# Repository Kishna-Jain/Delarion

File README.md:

# Delarion

### A custom CoreXY 3D printer: the best bang for your buck

Delarion is a CoreXY 3D printer designed to deliver near-premium performance without a premium price. It is built on a rigid **2020 aluminum extrusion** frame, with **ball screws** and **linear rails** for smooth, accurate motion, and runs **Klipper** on a custom **ESP32-S3** control board.

> **Status:** Design / pre-build. Submitted to Hack Club Stardance for funding.

---

## Table of Contents

1. [Why Delarion?](#why-delarion)
2. [Highlights](#highlights)
3. [Specifications](#specifications)
4. [Motion System](#motion-system)
5. [Electronics and Firmware](#electronics-and-firmware)
6. [Custom PCB](#custom-pcb)
7. [3D Model](#3d-model)
8. [Roadmap](#roadmap)
9. [Credits](#credits)

---

## Why Delarion?

Every maker eventually gets the urge to build random nerdy things from YouTube tutorials. I went down that road too, but without a 3D printer the workarounds get messy, and the final result lacks finesse: a pile of scraps in a makeshift enclosure. We've all been there.

So I went shopping for a cheap printer, and the results weren't great. Printers now start around $100 USD, but most of those are disappointing, and there is little reason to buy an Ender 3 today when almost everything is better. Bambu Lab is an option, and some budget machines exist, but still nothing fully satisfying. In my area, a *good* printer costs about **$500**, while the cheap ones are just cheap.

So the quest began: **build my own.** Delarion is the result.

## Highlights

- **CoreXY kinematics** for fast, light-toolhead motion
- **2020 aluminum extrusion frame**, sturdy, rigid and easy to source
- **Ball screws and linear rails** for smooth, precise, quiet movement
- **Klipper firmware** running on a host computer for high speed and advanced features
- **ESP32-S3 main MCU**, with Wi-Fi/BLE and plenty of room for experiments
- **TMC2208 stepper drivers** for quiet operation
- **MPU6050 accelerometer on the board** for input shaping / resonance tuning
- **Fully custom PCB**, designed from scratch

## Specifications

| Item | Detail |
|---|---|
| Kinematics | CoreXY |
| Frame | 2020 aluminum extrusion |
| Linear motion | Linear rails |
| Z motion | Ball screws |
| Motors | NEMA 17 steppers |
| Stepper drivers | TMC2208 |
| Main MCU | ESP32-S3 |
| Firmware | Klipper |
| Host | Raspberry Pi or any spare laptop/PC |
| Input power | 24 V clean DC supply |
| Logic power | 5 V external, 3.3 V regulated on-board (AMS1117-3.3) |
| Input shaping sensor | MPU6050 |
| Build volume | _TBD_ |
| Max speed / acceleration | _TBD_ |
| Hotend / extruder | Standard hotend and extruder (see `BOM.csv`) |

<!-- TODO: fill in the TBD rows as the design is finalised -->

## Motion System

CoreXY moves the toolhead in X and Y using two fixed motors and a crossed belt path. Because the motors are stationary, the moving mass is small, which allows higher accelerations and cleaner prints than a traditional bed slinger.

- **X/Y:** two NEMA 17 motors driving a CoreXY belt layout on linear rails
- **Z:** ball screws for precise, repeatable vertical motion
- **Bed motion:** designed around the mechanism explained in MistsuMakes' tutorials (see [Credits](#credits))

New to CoreXY? [3ddistributed.com](https://3ddistributed.com) has the best infographics for understanding how the belt path works.

## Electronics and Firmware

### Why Klipper?

1. **Speed:** Klipper offloads heavy computation to a host microprocessor, giving a huge speed advantage over firmware that runs everything on the MCU.
2. **Accessibility:** Everyone has an old laptop or a Raspberry Pi lying around, so no expensive controller is needed.
3. **Documentation:** Klipper's docs are excellent and thorough.

### Why ESP32-S3?

It is cheap, powerful, and has built-in wireless, which opens up endless possibilities for experimenting with new features.

### Software stack

- Klipper (firmware on MCU, host software on Pi/PC)
- Moonraker (API) and a web UI such as Mainsail or Fluidd _(recommended)_

<!-- TODO: add printer.cfg and Klipper MCU build/flash instructions -->

## Custom PCB

A deliberately simple custom board built around the ESP32-S3.

**On board:**

- ESP32-S3 MCU
- TMC2208 stepper drivers
- MPU6050 accelerometer
- AMS1117-3.3 regulator for the 3.3 V logic rail
- IRLZ44N MOSFET(s) for heater/fan switching

> **Key notes**
>
> - **Power:** the board needs a **clean 24 V supply**. Poor-quality power will cause problems.
> - **External 24 V and 5 V:** the XL103 step-down converter is **not mounted on the PCB** because it produces too much heat. Provide clean 24 V and 5 V from an external converter to the designated pins, with **active cooling** on the converter.
> - **3.3 V rail:** regulated on-board by an AMS1117-3.3.
> - **Driver cooling:** fit heatsinks and active cooling to the TMC2208/2209 drivers, otherwise the risk of damage is high.
> - **Designed in KiCad 10.**
> - **IRLZ44N placement:** mount the IRLZ44N on the **bottom** of the board, **not the top**.
> - **Honest disclaimer:** this is my first PCB. It isn't beautiful or well laid out, but it works, or at least that's what I'm hoping for. Revisions are expected.

<!-- TODO: add schematic PDF, Gerbers, and pinout table -->

## 3D Model

Explore the full CAD model on Onshape:

**[Open in Onshape](https://cad.onshape.com/documents/ddc5642abc531e1225c0dc8b/w/1fb68ecf66842d529f7141f3/e/0a949859a3af9baaf41af0a4)**

## Roadmap

- [x] CAD design
- [x] First PCB design
- [ ] Full CAD assembly STEP, Klipper config and firmware notes added to repo
- [ ] Order parts (pending Stardance funding)
- [ ] Frame and motion assembly
- [ ] PCB bring-up and Klipper configuration
- [ ] First print
- [ ] Input shaping and tuning
- [ ] PCB revision 2
- [ ] Full documentation and BOM

## Credits

This project wouldn't exist without a lot of people:

- **[Hack Club](https://hackclub.com):** this project was only possible because of them. They helped me find the right people and pushed me to go build my dream.
- **Stardance:** I'm submitting this project for funding, fingers crossed!
- **@RaygunRupe:** I was going to buy parts and figure it out on the fly. The only reason I went this deep into design and polish is because of this guy. Otherwise I'd have skipped the CAD work and made a mess.
- **MistsuMakes (YouTube):** his tutorials taught me how the motion system and the bed mechanism work. His video is what made me decide, "yeah, let's do it, I can make this too."
- **[3ddistributed.com](https://3ddistributed.com):** probably the best site for understanding how CoreXY works. After countless tutorials, its infographics finally made it click.
- **The Slack hardware community:** they helped me figure out how all of this works and connected me with people who helped me build it.

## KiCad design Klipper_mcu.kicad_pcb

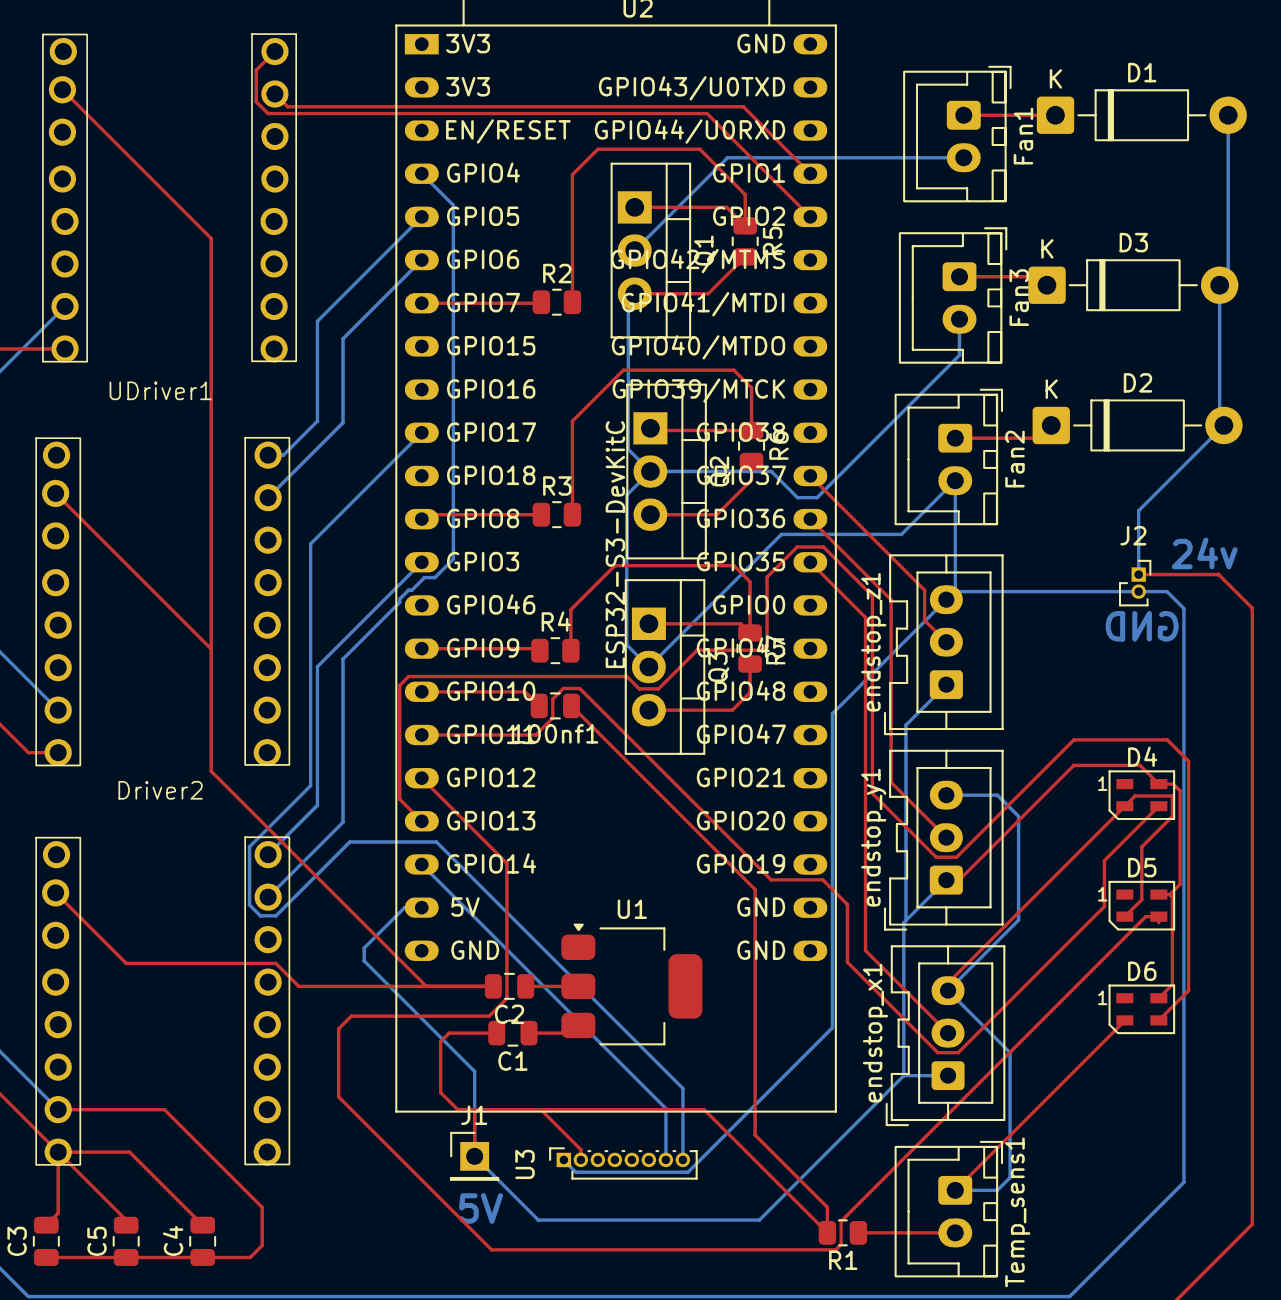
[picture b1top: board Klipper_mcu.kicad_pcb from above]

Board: 2 copper layers, 37 parts (0 on the bottom side), 35 nets.

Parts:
100nf1: C; C_0805_2012Metric
C1, C2: 10uf; C_0805_2012Metric
C3, C4, C5: 100uf; C_0805_2012Metric
D1, D2, D3: 1N4007; D_DO-41_SOD81_P10.16mm_Horizontal
D4, D5, D6: SK6805; LED_SK6805_PLCC4_2.4x2.7mm_P1.3mm
Driver1: 100uf; TMC2208
Driver2: TMC2208
Fan1, Fan2, Fan3: Conn_01x02_Pin; JST_XH_B2B-XH-A_1x02_P2.50mm_Vertical
J1: Conn_01x01_Socket; PinHeader_1x01_P2.54mm_Vertical
J2: Conn_01x02_Socket; PinSocket_1x02_P1.00mm_Vertical
Q1, Q2, Q3: IRLZ44N; TO-220-3_Vertical
R1: 4.7k ohm; R_0805_2012Metric
R2: 220 ohm; R_0805_2012Metric
R3, R4: 220ohm; R_0805_2012Metric
R5, R6, R7: 10k; R_0805_2012Metric
Temp_sens1: Conn_01x02; JST_XH_B2B-XH-A_1x02_P2.50mm_Vertical
U1: AMS1117-3.3; SOT-223-3_TabPin2
U2: ESP32-S3-DevKitC
U3: PinSocket_1x08_P1.00mm_Vertical
UDriver1: TMC2208
endstop_x1: Conn_01x03_Socket; JST_XA_B03B-XASK-1_1x03_P2.50mm_Vertical
endstop_y1: Conn_01x03_Socket; JST_XA_B03B-XASK-1_1x03_P2.50mm_Vertical
endstop_z1: Conn_01x03_Socket; JST_XA_B03B-XASK-1_1x03_P2.50mm_Vertical

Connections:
/3v3: C2.2, Driver1.2 (VIO), Driver2.2 (VIO), U2.1 (3V3), U2.2 (3V3), UDriver1.2 (VIO)
/5v: 100nf1.1, C1.2, D4.4 (VDD), D5.4 (VDD), D6.4 (VDD), R1.2, U2.21 (5V), U3.2 (VCC), endstop_x1.1, endstop_y1.1, endstop_z1.1
/24v: C3.2, C4.2, C5.2, D1.2 (A), D2.2 (A), D3.2 (A), Driver1.8 (VM), Driver2.8 (VM), J2.1, UDriver1.8 (VM)
/GND: C3.1, C4.1, C5.1, D4.2 (VSS), D5.2 (VSS), D6.2 (VSS), Driver1.7 (GND), Driver2.7 (GND), Fan2.2, Fan3.2, J2.2, Q1.3 (S), Q2.2 (D), Q2.3 (S), Q3.2 (D), Q3.3 (S), R5.2, R6.2, R7.2, Temp_sens1.1, U1.1 (GND), U3.1 (GND), UDriver1.7 (GND), endstop_x1.3, endstop_y1.3, endstop_z1.3
/GPIO1: Driver1.10 (STEP), U2.41 (GPIO1/ADC1_CH0)
/GPIO2: Driver1.9 (DIR), U2.40 (GPIO2/ADC1_CH1)
/GPIO3: Driver2.9 (DIR), U2.13 (GPIO3/ADC1_CH2)
/GPIO4: Driver2.10 (STEP), U2.4 (GPIO4/ADC1_CH3)
/GPIO5: U2.5 (GPIO5/ADC1_CH4), UDriver1.9 (DIR)
/GPIO6: U2.6 (GPIO6/ADC1_CH5), UDriver1.10 (STEP)
/GPIO7: R2.1, U2.7 (GPIO7/ADC1_CH6)
/GPIO8: R3.1, U2.12 (GPIO8/ADC1_CH7)
/GPIO9: R4.1, U2.15 (GPIO9/ADC1_CH8)
/GPIO10: 100nf1.2, U2.16 (GPIO10/ADC1_CH9)
/GPIO11: D4.3 (DIN), U2.17 (GPIO11/ADC2_CH0)
/GPIO12: D5.3 (DIN), U2.18 (GPIO12/ADC2_CH1)
/GPIO13: D6.3 (DIN), U2.19 (GPIO13/ADC2_CH2)
/GPIO14: U2.20 (GPIO14/ADC2_CH3), U3.7 (SDA)
/GPIO15: U2.10 (GPIO17/ADC2_CH6), U3.8 (SCL)
/GPIO35: U2.32 (GPIO35), endstop_x1.2
/GPIO36: U2.33 (GPIO36), endstop_y1.2
/GPIO37: U2.34 (GPIO37), endstop_z1.2
/MC1: Driver1.5 (M1A), Driver2.5 (M1A), UDriver1.5 (M1A)
/MC2: Driver1.3 (M2B), Driver2.3 (M2B), UDriver1.3 (M2B)
unnamed: D1.1 (K), Fan1.1
unnamed: D2.1 (K), Fan2.1
unnamed: D3.1 (K), Fan3.1
unnamed: Fan1.2, Q1.2 (D)
unnamed: Q1.1 (G), R2.2, R5.1
unnamed: Q2.1 (G), R3.2, R6.1
unnamed: Q3.1 (G), R4.2, R7.1
unnamed: R1.1, Temp_sens1.2
unnamed: C1.1, U1.3 (VI)
unnamed: C2.1, U1.2 (VO)
unnamed: U2.22 (GND), U2.23 (GND), U2.24 (GND), U2.44 (GND)

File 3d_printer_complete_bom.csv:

Item Description,Quantity,Price (INR) per unit (approx with 5% markup),Total Price (INR)
Ballscrew Kit (300mm with end machining),2,2730,5460
MGN12H Linear Rails with Carriage Blocks (300mm),3,5040,15120
GT2 Timing Pulley (20 Teeth),4,275,1100
GT2 Open Timing Belt (6mm width),4,361,1444
GT2 Timing Idler Pulleys,4,336,1344
NEMA 17 Stepper Motors (D-Type Shaft),4,3238,12952
2020 V-Slot Aluminum Extrusion Profiles (1M lengths),4,2054,8216
T-Shape Corner Bracket Plates for 2020,4,525,2100
Ball Screw End Support Bearings (BK/BF12),2,630,1260
NEMA 17 Stepper Motor Mounting Brackets,2,422,844
2020 Cast Corner Brackets,24,62.75,1506
M5 Hammer / Sliding Nuts,100,2.63,263
M3 Hammer / Sliding Nuts,15,3.53,53
"M5 Button Head Screws (8mm, 13mm, 16mm, 20mm mix)",80,3.29,263
M5 T-Nuts,12,9.17,110
M3 Screws (12mm),16,3.31,53
3D Printed Custom Parts,1,1050,1050
100nf Capacitor (C_0805),1,5.25,5.25
"10uf Capacitor (C_0805) [C1, C2]",2,5.25,10.5
"100uf Capacitor (C_0805) [C3, C4, C5]",3,7.35,22.05
"1N4007 Diode [D1, D2, D3]",3,12.6,37.8
"SK6805 LED [D4, D5, D6]",3,14.7,44.1
TMC2208 Stepper Driver (Driver1),1,283.5,283.5
"TMC2208 Stepper Driver (Driver2, UDriver1)",2,283.5,567
JST 3-Pin Socket Connector [Endstops],3,10.5,31.5
JST 2-Pin Pin Connector [Fans 1-3],3,10.5,31.5
Pin Header 1x01 Socket [J1],1,10.5,10.5
Pin Socket 1x02 [J2],1,10.5,10.5
"IRLZ44N MOSFET [Q1, Q2, Q3]",3,42,126
4.7k ohm Resistor (R1),1,5.25,5.25
220 ohm Resistor (R2),1,5.25,5.25
"220 ohm Resistor [R3, R4]",2,5.25,10.5
"10k Resistor [R5, R6, R7]",3,5.25,15.75
JST 2-Pin Connector [Temp Sensor],1,10.5,10.5
AMS1117-3.3 Voltage Regulator [U1],1,11.55,11.55
ESP32-S3-DevKitC [U2],1,882,882
MPU6050 Accelerometer [U3],1,157.5,157.5
Step Down Converter [XL103],1,84,84
,,Total price,55500.5
